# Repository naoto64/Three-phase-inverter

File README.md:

# Three-phase-inverter
Three-phase inverter operating at AC100V.

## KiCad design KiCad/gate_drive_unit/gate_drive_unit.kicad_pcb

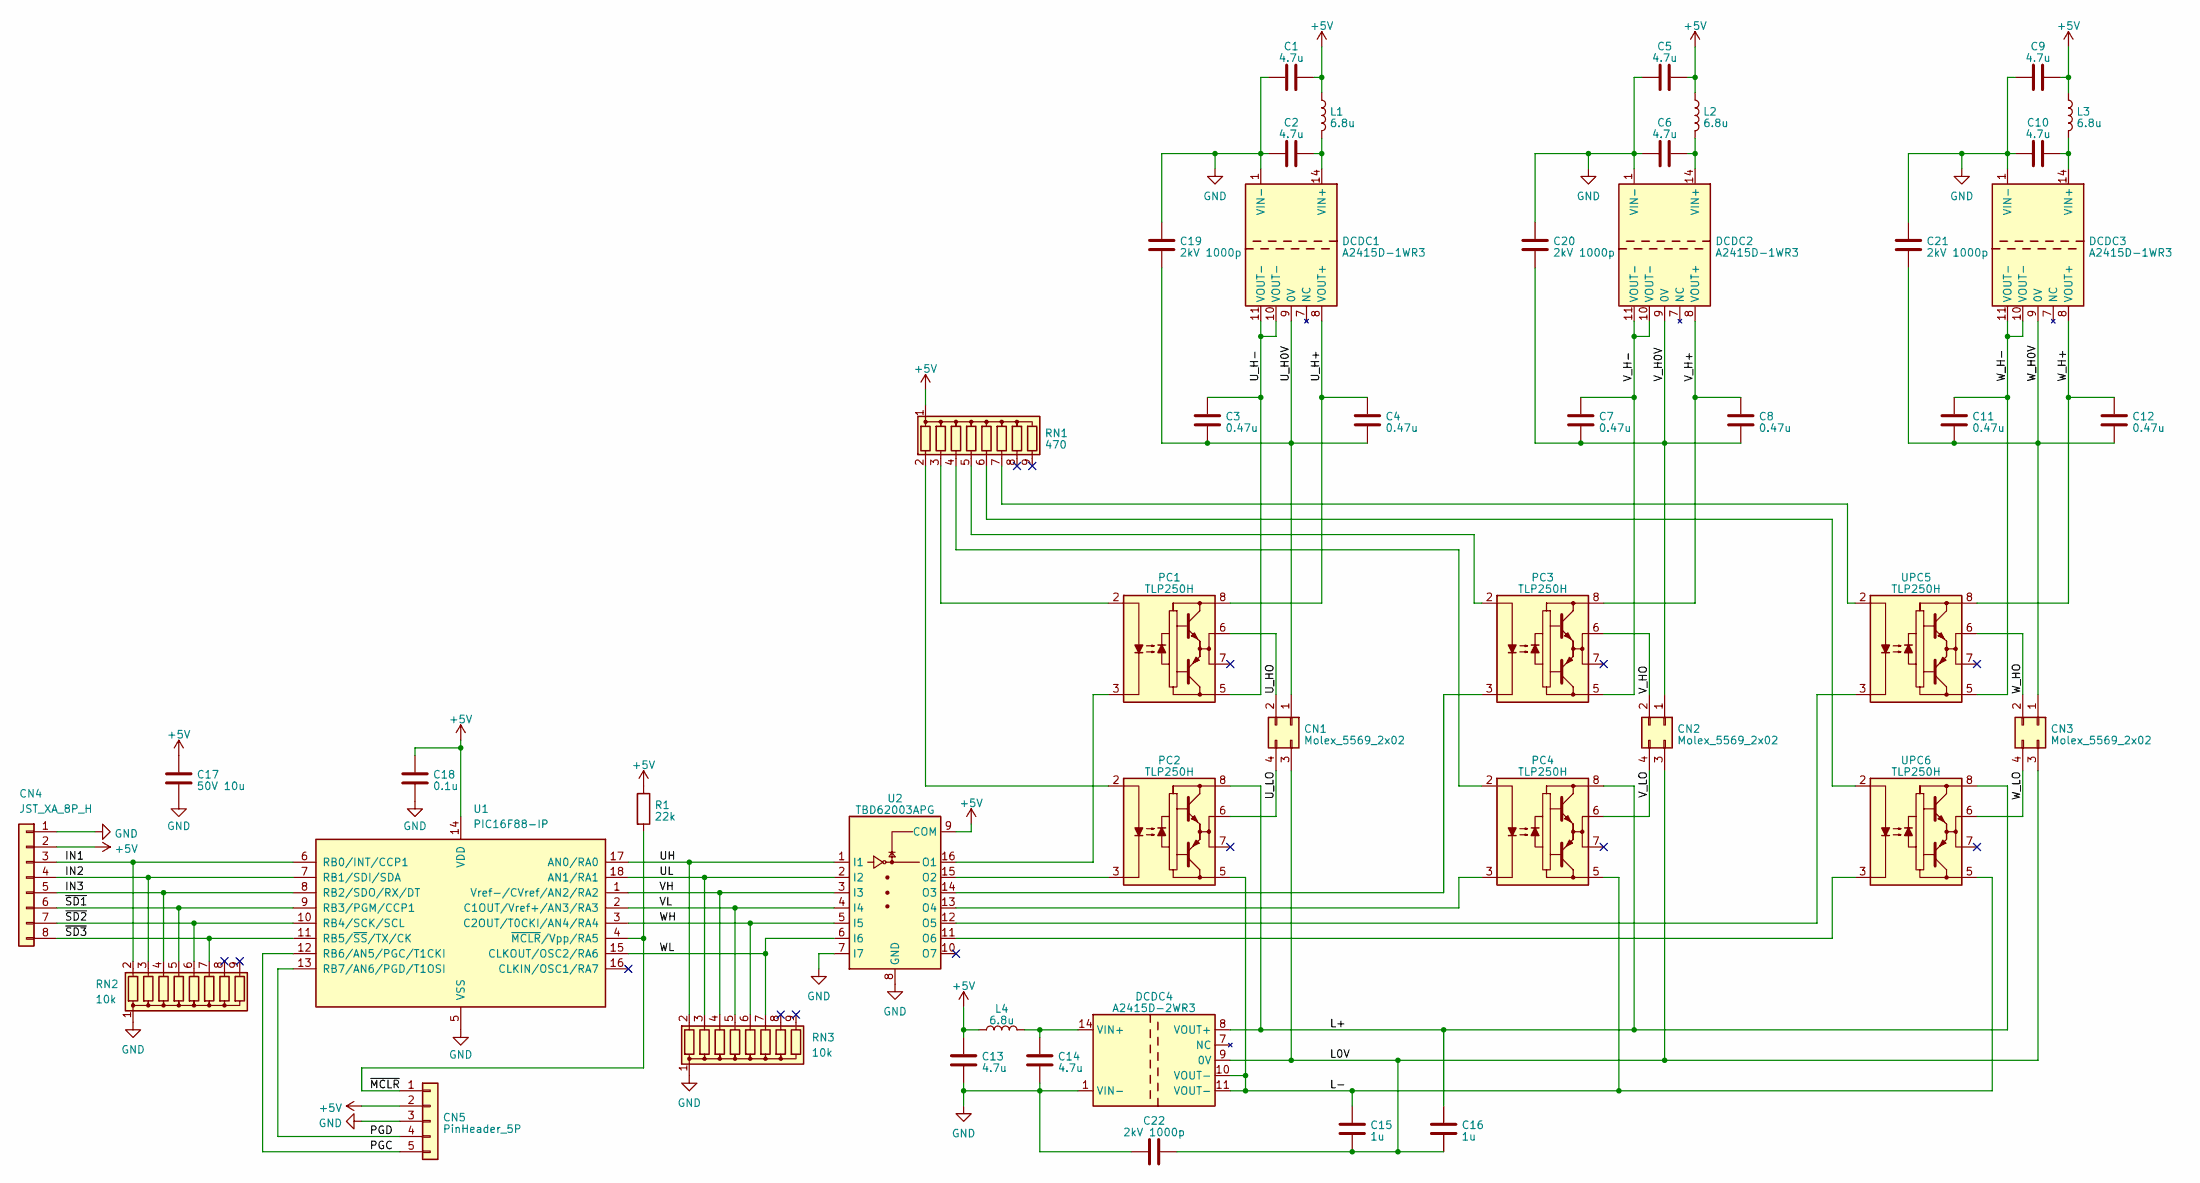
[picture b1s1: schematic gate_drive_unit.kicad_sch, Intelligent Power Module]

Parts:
C1, C2, C5, C6, C9, C10, C13, C14: 4.7u; C_Disc_D5.0mm_W2.5mm_P5.00mm
C3, C4, C7, C8, C11, C12: 0.47u; C_Disc_D5.0mm_W2.5mm_P2.50mm
C15, C16: 1u; C_Disc_D5.0mm_W2.5mm_P5.00mm
C17: 50V 10u; C_Disc_D5.0mm_W2.5mm_P5.00mm
C18: 0.1u; C_Disc_D5.0mm_W2.5mm_P5.00mm
C19, C20, C21, C22: 2kV 1000p; C_Disc_D6.0mm_W4.4mm_P5.00mm
CN1, CN2, CN3: Molex_5569_2x02; Molex_Mini-Fit_Jr_5569-04A1_2x02_P4.20mm_Horizontal
CN4: JST_XA_8P_H; JST_XA_S08B-XASK-1N-BN_1x08_P2.50mm_Horizontal
CN5: PinHeader_5P; PinHeader_1x05_P2.54mm_Vertical
DCDC1, DCDC2, DCDC3: A2415D-1WR3; DIP-14_W7.62mm_Socket
DCDC4: A2415D-2WR3; DIP-14_W7.62mm_Socket
L1, L2, L3, L4: 6.8u; L_Axial_L7.0mm_D3.3mm_P2.54mm_Vertical_Fastron_MICC
PC1, PC2, PC3, PC4: TLP250H; DIP-8_W7.62mm_Socket
R1: 22k; R_Axial_DIN0204_L3.6mm_D1.6mm_P2.54mm_Vertical
RN1: 470; R_Array_SIP9
RN2, RN3: 10k; R_Array_SIP9
U1: PIC16F88-IP; DIP-18_W7.62mm_Socket
U2: TBD62003APG; DIP-16_W7.62mm
UPC5, UPC6: TLP250H; DIP-8_W7.62mm_Socket

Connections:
+5V: C1.2, C5.2, C9.2, C13.1, C17.1, C18.1, CN4.2, CN5.2, L1.1, L2.1, L3.1, L4.1, R1.1, RN1.1 (common), U1.14 (VDD), U2.9 (COM)
/IN1: CN4.3, RN2.2 (R1), U1.6 (RB0/INT/CCP1)
/IN2: CN4.4, RN2.3 (R2), U1.7 (RB1/SDI/SDA)
/IN3: CN4.5, RN2.4 (R3), U1.8 (RB2/SDO/RX/DT)
/L0V: C15.2, C16.1, C22.1, CN1.3, CN2.3, CN3.3, DCDC4.9 (0V)
/L+: C16.2, DCDC4.8 (VOUT+), PC2.8 (VCC), PC4.8 (VCC), UPC6.8 (VCC)
/L-: C15.1, DCDC4.10 (VOUT-), DCDC4.11 (VOUT-), PC2.5 (VEE), PC4.5 (VEE), UPC6.5 (VEE)
/PGC: CN5.5, U1.12 (RB6/AN5/PGC/T1CKI)
/PGD: CN5.4, U1.13 (RB7/AN6/PGD/T1OSI)
/UH: RN3.2 (R1), U1.17 (AN0/RA0), U2.1 (I1)
/UL: RN3.3 (R2), U1.18 (AN1/RA1), U2.2 (I2)
/U_H0V: C3.2, C4.1, C19.2, CN1.1, DCDC1.9 (0V)
/U_H+: C4.2, DCDC1.8 (VOUT+), PC1.8 (VCC)
/U_H-: C3.1, DCDC1.10 (VOUT-), DCDC1.11 (VOUT-), PC1.5 (VEE)
/U_HO: CN1.2, PC1.6 (VO)
/U_LO: CN1.4, PC2.6 (VO)
/VH: RN3.4 (R3), U1.1 (Vref-/CVref/AN2/RA2), U2.3 (I3)
/VL: RN3.5 (R4), U1.2 (C1OUT/Vref+/AN3/RA3), U2.4 (I4)
/V_H0V: C7.2, C8.1, C20.2, CN2.1, DCDC2.9 (0V)
/V_H+: C8.2, DCDC2.8 (VOUT+), PC3.8 (VCC)
/V_H-: C7.1, DCDC2.10 (VOUT-), DCDC2.11 (VOUT-), PC3.5 (VEE)
/V_HO: CN2.2, PC3.6 (VO)
/V_LO: CN2.4, PC4.6 (VO)
/WH: RN3.6 (R5), U1.3 (C2OUT/T0CKI/AN4/RA4), U2.5 (I5)
/WL: RN3.7 (R6), U1.15 (CLKOUT/OSC2/RA6), U2.6 (I6)
/W_H0V: C11.2, C12.1, C21.2, CN3.1, DCDC3.9 (0V)
/W_H+: C12.2, DCDC3.8 (VOUT+), UPC5.8 (VCC)
/W_H-: C11.1, DCDC3.10 (VOUT-), DCDC3.11 (VOUT-), UPC5.5 (VEE)
/W_HO: CN3.2, UPC5.6 (VO)
/W_LO: CN3.4, UPC6.6 (VO)
/~MCLR: CN5.1, R1.2, U1.4 (~MCLR/Vpp/RA5)
/~SD1: CN4.6, RN2.5 (R4), U1.9 (RB3/PGM/CCP1)
/~SD2: CN4.7, RN2.6 (R5), U1.10 (RB4/SCK/SCL)
/~SD3: CN4.8, RN2.7 (R6), U1.11 (RB5/~SS/TX/CK)
GND: C1.1, C2.1, C5.1, C6.1, C9.1, C10.1, C13.2, C14.2, C17.2, C18.2, C19.1, C20.1, C21.1, C22.2, CN4.1, CN5.3, DCDC1.1 (VIN-), DCDC2.1 (VIN-), DCDC3.1 (VIN-), DCDC4.1 (VIN-), RN2.1 (common), RN3.1 (common), U1.5 (VSS), U2.7 (I7), U2.8 (GND)
unnamed: C2.2, DCDC1.14 (VIN+), L1.2
unnamed: C6.2, DCDC2.14 (VIN+), L2.2
unnamed: C10.2, DCDC3.14 (VIN+), L3.2
unnamed: C14.1, DCDC4.14 (VIN+), L4.2
unnamed: PC1.2 (A), RN1.3 (R2)
unnamed: PC1.3 (C), U2.16 (O1)
unnamed: PC2.2 (A), RN1.2 (R1)
unnamed: PC2.3 (C), U2.15 (O2)
unnamed: PC3.2 (A), RN1.5 (R4)
unnamed: PC3.3 (C), U2.14 (O3)
unnamed: PC4.2 (A), RN1.4 (R3)
unnamed: PC4.3 (C), U2.13 (O4)
unnamed: RN1.6 (R5), UPC6.2 (A)
unnamed: RN1.7 (R6), UPC5.2 (A)
unnamed: U2.12 (O5), UPC5.3 (C)
unnamed: U2.11 (O6), UPC6.3 (C)

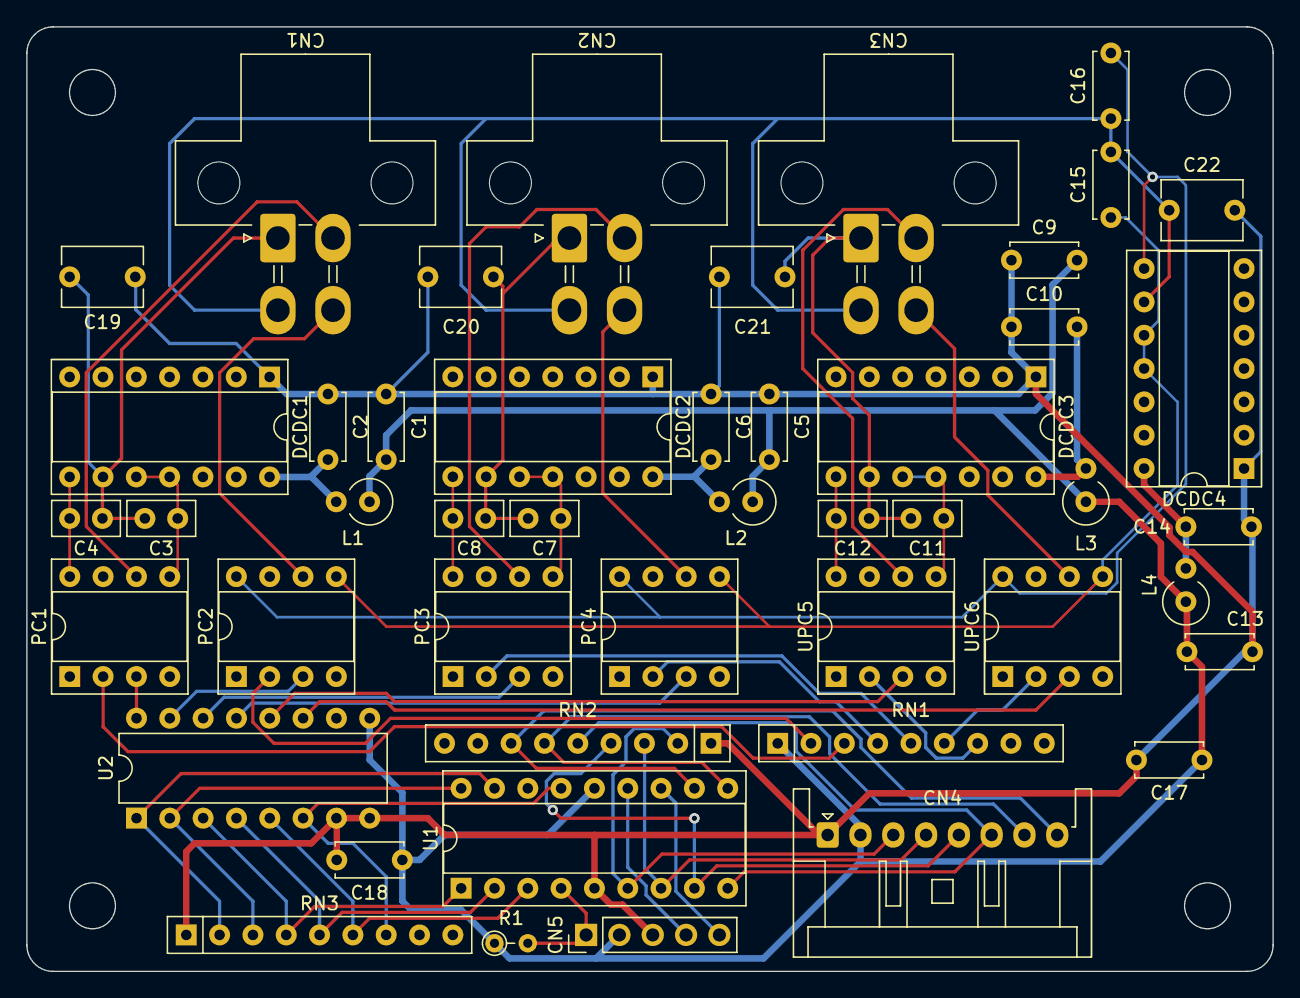
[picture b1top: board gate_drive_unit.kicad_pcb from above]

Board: 2 copper layers, 95.0 x 72.0 mm, 47 parts (0 on the bottom side), 51 nets.

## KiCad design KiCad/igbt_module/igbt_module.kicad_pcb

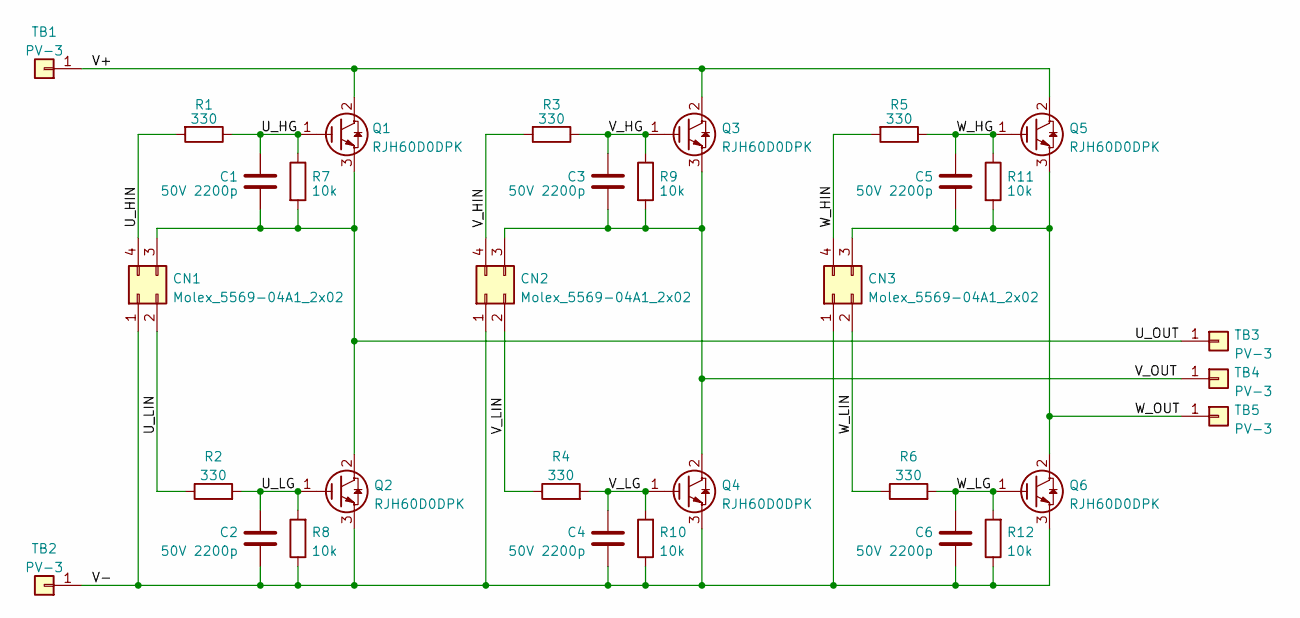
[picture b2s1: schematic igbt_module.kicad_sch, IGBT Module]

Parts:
C1, C2, C3, C4, C5, C6: 50V 2200p; C_Disc_D5.0mm_W2.5mm_P2.50mm
CN1, CN2, CN3: Molex_5569-04A1_2x02; Molex_Mini-Fit_Jr_5566-04A_2x02_P4.20mm_Vertical
Q1, Q2, Q3, Q4, Q5, Q6: RJH60D0DPK; TO-3P-3_Vertical
R1, R2, R3, R4, R5, R6: 330; R_Axial_DIN0204_L3.6mm_D1.6mm_P2.54mm_Vertical
R7, R9, R11: 10k; R_Axial_DIN0204_L3.6mm_D1.6mm_P2.54mm_Vertical
R8, R10, R12: 10k; R_Axial_DIN0207_L6.3mm_D2.5mm_P7.62mm_Horizontal
TB1, TB2: PV-3
TB3, TB4, TB5: PV-3; PV-3_Both

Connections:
/U_HG: C1.1, Q1.1 (G), R1.1, R7.1
/U_HIN: CN1.4, R1.2
/U_LG: C2.2, Q2.1 (G), R2.2, R8.2
/U_LIN: CN1.2, R2.1
/U_OUT: C1.2, CN1.3, Q1.3 (E), Q2.2 (C), R7.2, TB3.1
/V+: Q1.2 (C), Q3.2 (C), Q5.2 (C), TB1.1
/V-: C2.1, C4.1, C6.1, CN1.1, CN2.1, CN3.1, Q2.3 (E), Q4.3 (E), Q6.3 (E), R8.1, R10.1, R12.1, TB2.1
/V_HG: C3.1, Q3.1 (G), R3.1, R9.1
/V_HIN: CN2.4, R3.2
/V_LG: C4.2, Q4.1 (G), R4.2, R10.2
/V_LIN: CN2.2, R4.1
/V_OUT: C3.2, CN2.3, Q3.3 (E), Q4.2 (C), R9.2, TB4.1
/W_HG: C5.1, Q5.1 (G), R5.1, R11.1
/W_HIN: CN3.4, R5.2
/W_LG: C6.2, Q6.1 (G), R6.2, R12.2
/W_LIN: CN3.2, R6.1
/W_OUT: C5.2, CN3.3, Q5.3 (E), Q6.2 (C), R11.2, TB5.1

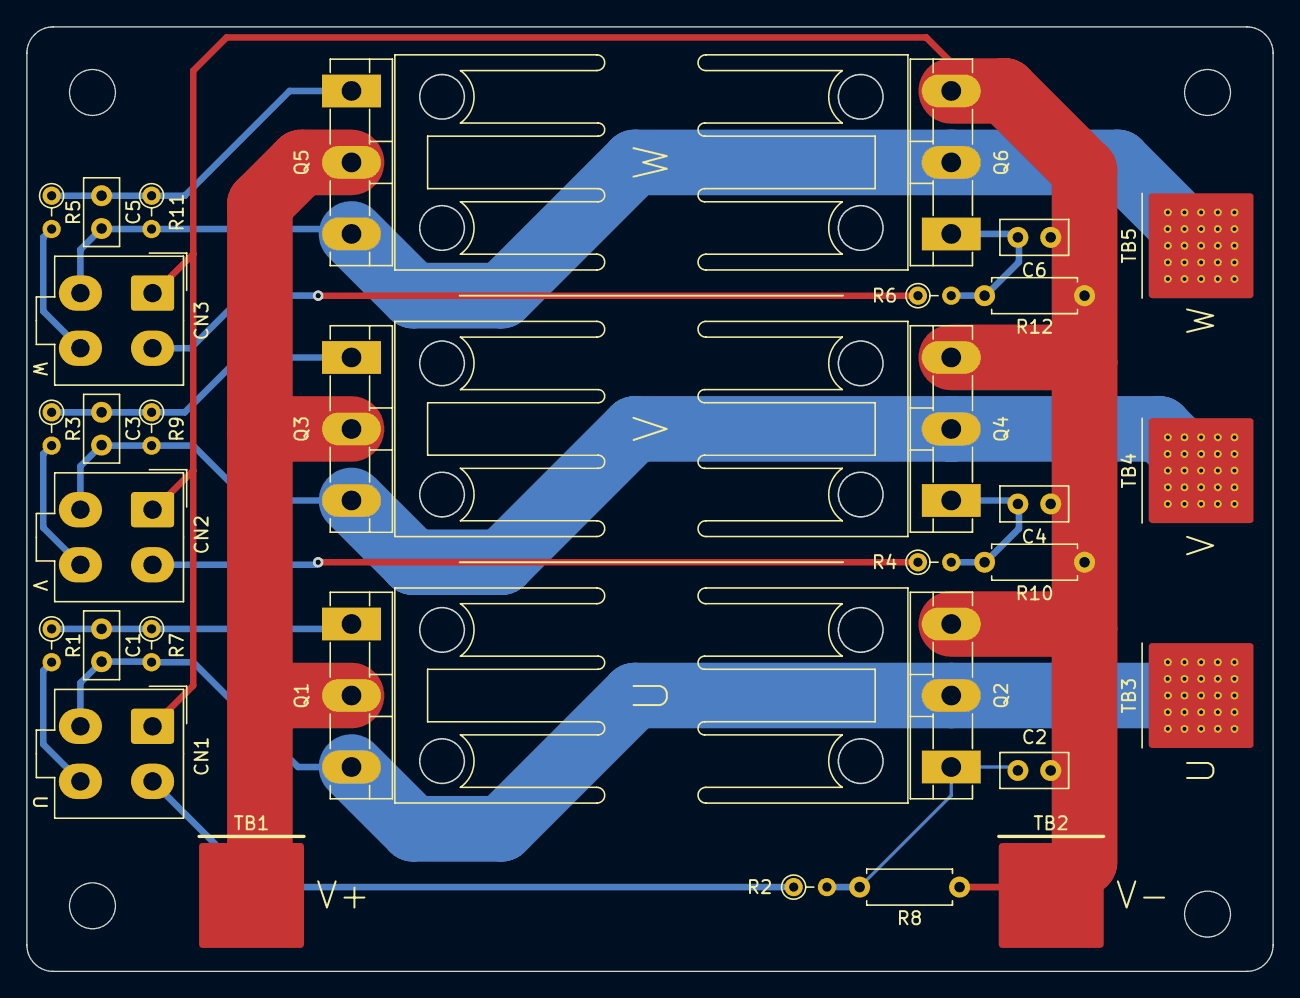
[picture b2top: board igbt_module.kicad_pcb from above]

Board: 2 copper layers, 95.0 x 72.0 mm, 32 parts (0 on the bottom side), 17 nets.

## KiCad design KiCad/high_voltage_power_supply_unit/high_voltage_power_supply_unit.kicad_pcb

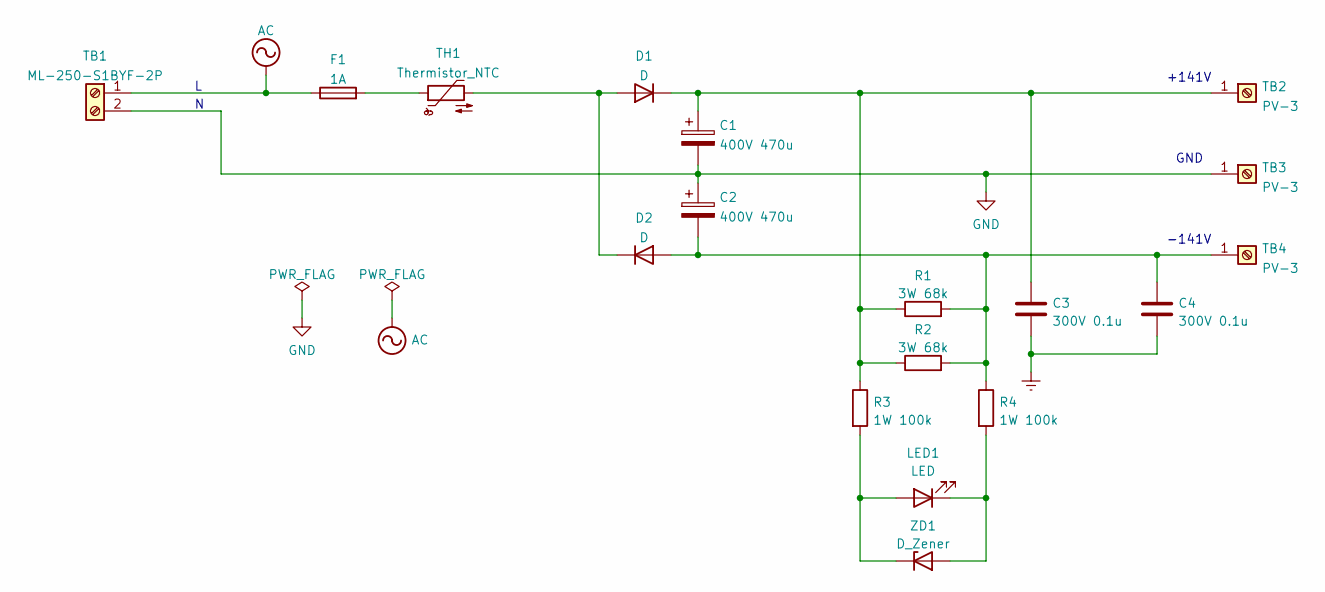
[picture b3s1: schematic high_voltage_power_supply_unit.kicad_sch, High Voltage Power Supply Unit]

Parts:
C1, C2: 400V 470u; CP_Radial_D30.0mm_P10.00mm_SnapIn
C3, C4: 300V 0.1u; C_Disc_D7.5mm_W4.4mm_P5.00mm
D1, D2: D; TO-220-2_Vertical
F1: 1A; F-200-N
LED1: LED; LED_D3.0mm_Clear
R1, R2: 3W 68k; R_Axial_DIN0617_L17.0mm_D6.0mm_P20.32mm_Horizontal
R3, R4: 1W 100k; R_Axial_DIN0309_L9.0mm_D3.2mm_P5.08mm_Vertical
TB1: ML-250-S1BYF-2P
TB2, TB3, TB4: PV-3
TH1: Thermistor_NTC; C_Rect_L10.0mm_W3.0mm_P7.50mm_MKS4
ZD1: D_Zener; D_DO-34_SOD68_P7.62mm_Horizontal

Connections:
AC: F1.1, TB1.1
Earth: C3.2, C4.2
GND: C1.2, C2.1, TB1.2, TB3.1
unnamed: C1.1, C3.1, D1.1 (K), R1.1, R2.1, R3.1, TB2.1
unnamed: C2.2, C4.1, D2.2 (A), R1.2, R2.2, R4.1, TB4.1
unnamed: D1.2 (A), D2.1 (K), TH1.2
unnamed: F1.2, TH1.1
unnamed: LED1.1 (K), R4.2, ZD1.2 (A)
unnamed: LED1.2 (A), R3.2, ZD1.1 (K)

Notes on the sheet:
GND
+141V
-141V

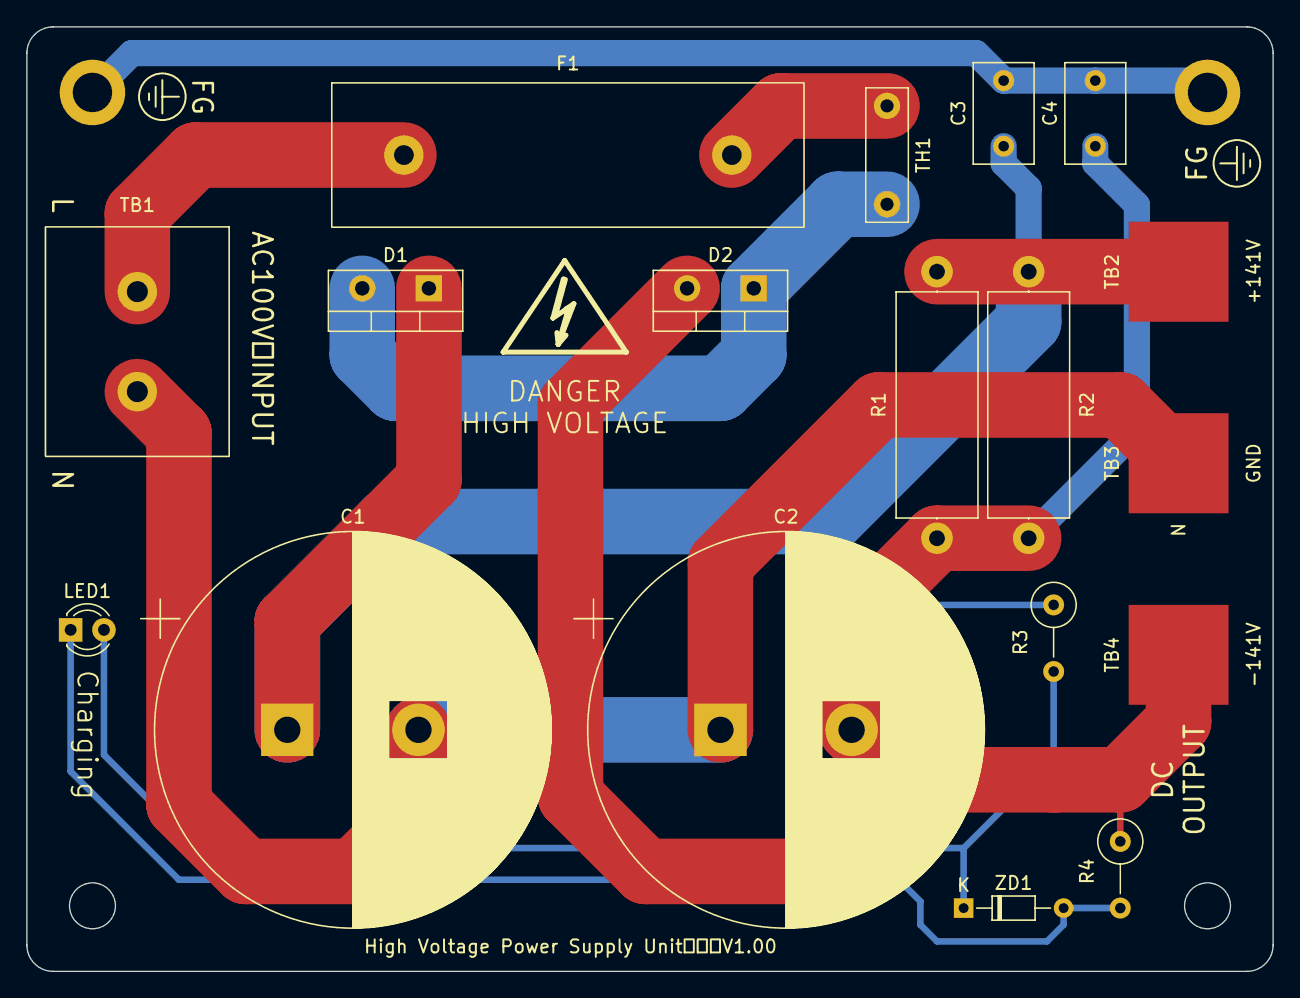
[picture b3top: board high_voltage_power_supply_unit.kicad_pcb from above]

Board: 2 copper layers, 95.0 x 72.0 mm, 18 parts (0 on the bottom side), 9 nets.

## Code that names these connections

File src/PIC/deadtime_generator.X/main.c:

/*
 * File:   main.c
 * Author: naoto
 *
 * Created on 2023/03/25, 18:41
 */


#include <xc.h>

#pragma config FOSC = INTOSC    // 内部クロックを使用
#pragma config PLLEN = ON       // PLLを有効化
#pragma config WDTE = OFF       // ウォッチドッグタイマーは使用しない
#pragma config CP = OFF         // コードプロテクションは無効
#pragma config LVP = OFF        // LVPは使用しない

#define _XTAL_FREQ 32000000
#define IN1 PORTBbits.RB0
#define IN2 PORTBbits.RB1
#define IN3 PORTBbits.RB2
#define SD1 PORTBbits.RB3
#define SD2 PORTBbits.RB4
#define SD3 PORTBbits.RB5
#define DEADTIME 10 // デッドタイム（10us）

#define U_OUT_H LATAbits.LATA0
#define U_OUT_L LATAbits.LATA1
#define V_OUT_H LATAbits.LATA2
#define V_OUT_L LATAbits.LATA3
#define W_OUT_H LATAbits.LATA4
#define W_OUT_L LATAbits.LATA6

void __interrupt() isr(void) {
    if (TMR2IF == 1) {
        // U相
        if (SD1 == 1) { // SD1がHighの場合
            if (IN1 == 1) {    // IN1がHighの場合
                if (U_OUT_L == 1) {   // ローサイド側がONの場合
                    U_OUT_H = 0;
                    U_OUT_L = 0;
                }
                else {
                    U_OUT_H = 1;
                    U_OUT_L = 0;
                }
            }
            else {  // IN1がLowの場合
                if (U_OUT_H == 1) {   // ハイサイド側がONの場合
                    U_OUT_H = 0;
                    U_OUT_L = 0;
                }
                else {
                    U_OUT_H = 0;
                    U_OUT_L = 1;
                }
            }
        }
        else {
            U_OUT_H = 0;
            U_OUT_L = 0;
        }
        
        // V相
        if (SD2 == 1) { // SD2がHighの場合
            if (IN2 == 1) {    // IN2がHighの場合
                if (V_OUT_L == 1) {   // ローサイド側がONの場合
                    V_OUT_H = 0;
                    V_OUT_L = 0;
                }
                else {
                    V_OUT_H = 1;
                    V_OUT_L = 0;
                }
            }
            else {  // IN2がLowの場合
                if (V_OUT_H == 1) {   // ハイサイド側がONの場合
                    V_OUT_H = 0;
                    V_OUT_L = 0;
                }
                else {
                    V_OUT_H = 0;
                    V_OUT_L = 1;
                }
            }
        }
        else {
            V_OUT_H = 0;
            V_OUT_L = 0;
        }
        
        // W相
        if (SD3 == 1) { // SD3がHighの場合
            if (IN3 == 1) {    // IN3がHighの場合
                if (W_OUT_L == 1) {   // ローサイド側がONの場合
                    W_OUT_H = 0;
                    W_OUT_L = 0;
                }
                else {
                    W_OUT_H = 1;
                    W_OUT_L = 0;
                }
            }
            else {  // IN3がLowの場合
                if (W_OUT_H == 1) {   // ハイサイド側がONの場合
                    W_OUT_H = 0;
                    W_OUT_L = 0;
                }
                else {
                    W_OUT_H = 0;
                    W_OUT_L = 1;
                }
            }
        }
        else {
            W_OUT_H = 0;
            W_OUT_L = 0;
        }
        // TMR2割り込みフラグをクリアする
        PIR1bits.TMR2IF = 0;
    }
    return;
}

void main(void) {
    /* ---------- クロック関連処理 ---------- */
    OSCCON = 0b01110000;
    
    /* ---------- IOポートの設定 ---------- */
    ANSELA = 0;         // すべてをデジタルモードに設定
    ANSELB = 0;         // すべてをデジタルモードに設定
    TRISA = 0b00000000; // RA0～RA7を出力に設定
    TRISB = 0b00111111; // RB0～RB5を入力に設定（RB6～7は出力に設定）
    LATA = 0b00000000;  // ポートAをすべてLowに設定
    
    /* ---------- 割り込み関連設定 ---------- */
    T2CON = 0b00000100; // TMR2プリスケーラ値を1倍、ポストスケーラ値は1:1の設定
    PR2 = 32 / 4 * DEADTIME - 1;    // タイマーのカウント値を設定 (32MHz / 4 * 5us - 1)
    TMR2 = 0;   // タイマー2の初期化
    TMR2IF = 0; // タイマー2割込フラグを0にする
    TMR2IE = 1; // タイマー2割込みを許可する
    PEIE = 1;   // 周辺装置割り込みを許可する
    GIE = 1;    // グローバル割り込みを許可する

    /* ---------- メインループ ---------- */
    while (1) {
    }
    return;
}

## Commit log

2022-03-24 Added KiCad schematic.
    First upload
2022-03-26 Creating a program for the ESP32.
    Creating a VVVF control program.
2022-03-27 Minor correction
    Corrected the waveform.
    Changed the array in asynchronous mode.
2022-03-30 Add PDF files.
2023-10-07 Update KiCad schematic data.
